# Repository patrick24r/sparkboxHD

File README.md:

# SparkboxHD
Sparkbox, now in 720p!  
The SparkboxHD is a device that will support 2D graphics
                      
### Build and Run
Build using

```
python3 build_sparkbox.py <device>
```

where `<device>` is an existing directory at `device/<device>`.

## MCU
User controller - 2 Analog sticks, 16 Buttons 

### OS
The OS allows the user to choose a level to load

### Levels

#### Loading a level
A level can only be as large as what can fit in memory

Audio data is decompressed and loaded to internal RAM
Video data is loaded to the GPU

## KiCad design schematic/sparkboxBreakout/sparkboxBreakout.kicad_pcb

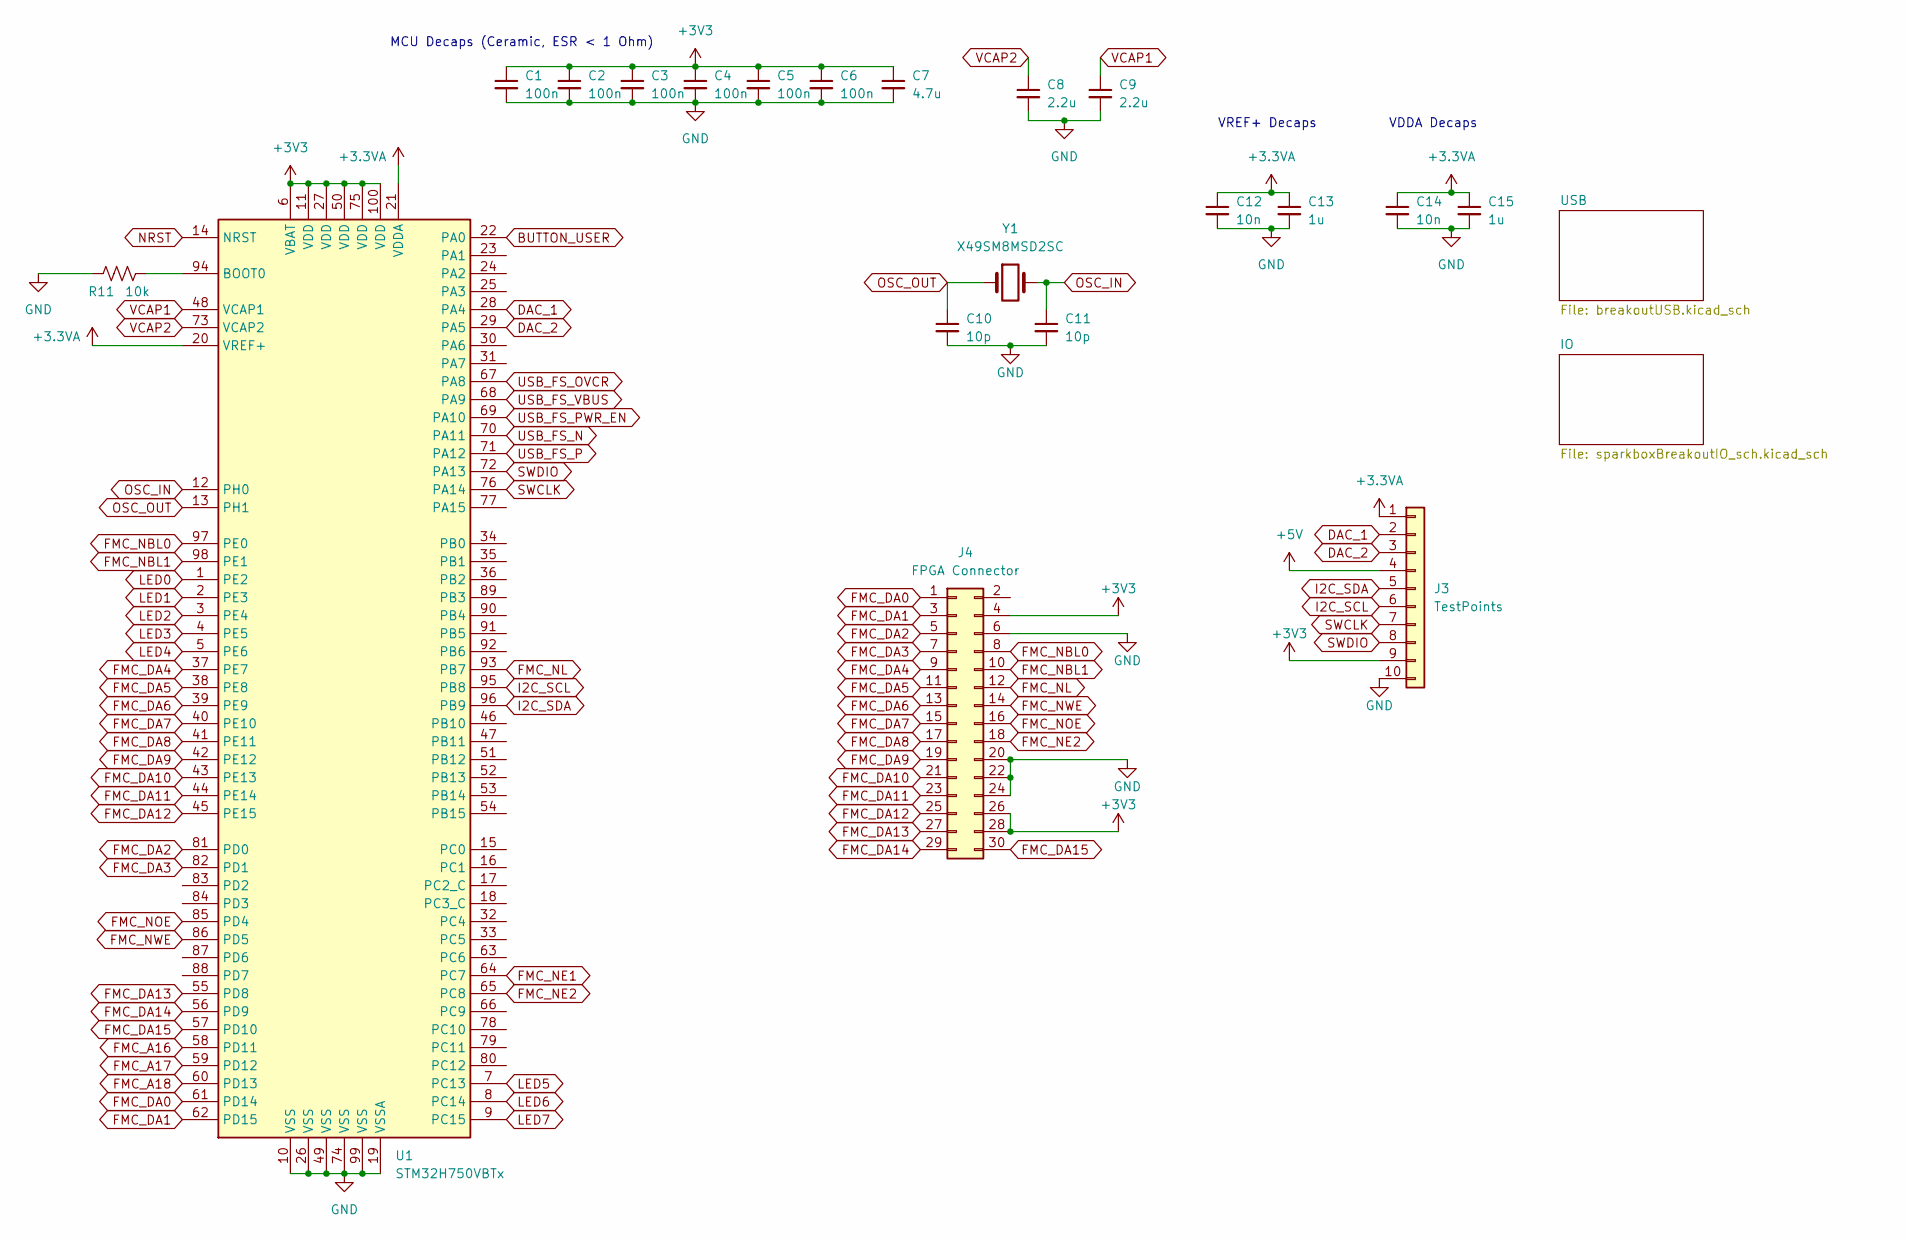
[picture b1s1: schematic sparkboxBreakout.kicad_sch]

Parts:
C1, C2, C3, C4, C5, C6: 100n; C_0402_1005Metric; JLCPCB Part # C1525
C7: 4.7u; C_0402_1005Metric; JLCPCB Part # C23733
C8, C9: 2.2u; C_0402_1005Metric; JLCPCB Part # C12530
C10, C11: 10p; C_0402_1005Metric; JLCPCB Part # C32949
C12, C14: 10n; C_0402_1005Metric; JLCPCB Part # C15195
C13, C15: 1u; C_0402_1005Metric; JLCPCB Part # C52923
J3: TestPoints; PinHeader_1x10_P2.54mm_Vertical; JLCPCB Part # C57369
J4: FPGA Connector; PinHeader_2x15_P2.54mm_Vertical; JLCPCB Part # C56496
R11: 10k; R_0402_1005Metric; JLCPCB Part # C25744
U1: STM32H750VBTx; LQFP-100_14x14mm_P0.5mm; JLCPCB Part # C404010
Y1: X49SM8MSD2SC; Crystal_SMD_HC49-SD; JLCPCB Part # C12674

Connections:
+3.3VA: C12.1, C13.1, C14.1, C15.1, J3.1, U1.20 (VREF+), U1.21 (VDDA); also elsewhere on the board
+3V3: C1.1, C2.1, C3.1, C4.1, C5.1, C6.1, C7.1, J3.9, J4.4, J4.26, J4.28, U1.6 (VBAT), U1.11 (VDD), U1.27 (VDD), U1.50 (VDD), U1.75 (VDD), U1.100 (VDD); also elsewhere on the board
+5V: J3.4; also elsewhere on the board
BUTTON_USER: U1.22 (PA0); also elsewhere on the board
DAC_1: J3.2, U1.28 (PA4)
DAC_2: J3.3, U1.29 (PA5)
FMC_A16: U1.58 (PD11)
FMC_A17: U1.59 (PD12)
FMC_A18: U1.60 (PD13)
FMC_DA0: J4.1, U1.61 (PD14)
FMC_DA1: J4.3, U1.62 (PD15)
FMC_DA2: J4.5, U1.81 (PD0)
FMC_DA3: J4.7, U1.82 (PD1)
FMC_DA4: J4.9, U1.37 (PE7)
FMC_DA5: J4.11, U1.38 (PE8)
FMC_DA6: J4.13, U1.39 (PE9)
FMC_DA7: J4.15, U1.40 (PE10)
FMC_DA8: J4.17, U1.41 (PE11)
FMC_DA9: J4.19, U1.42 (PE12)
FMC_DA10: J4.21, U1.43 (PE13)
FMC_DA11: J4.23, U1.44 (PE14)
FMC_DA12: J4.25, U1.45 (PE15)
FMC_DA13: J4.27, U1.55 (PD8)
FMC_DA14: J4.29, U1.56 (PD9)
FMC_DA15: J4.30, U1.57 (PD10)
FMC_NBL0: J4.8, U1.97 (PE0)
FMC_NBL1: J4.10, U1.98 (PE1)
FMC_NE1: U1.64 (PC7)
FMC_NE2: J4.18, U1.65 (PC8)
FMC_NL: J4.12, U1.93 (PB7)
FMC_NOE: J4.16, U1.85 (PD4)
FMC_NWE: J4.14, U1.86 (PD5)
GND: C1.2, C2.2, C3.2, C4.2, C5.2, C6.2, C7.2, C8.2, C9.2, C10.2, C11.2, C12.2, C13.2, C14.2, C15.2, J3.10, J4.6, J4.20, J4.22, J4.24, R11.2, U1.10 (VSS), U1.19 (VSSA), U1.26 (VSS), U1.49 (VSS), U1.74 (VSS), U1.99 (VSS); also elsewhere on the board
I2C_SCL: J3.6, U1.95 (PB8)
I2C_SDA: J3.5, U1.96 (PB9)
LED0: U1.1 (PE2); also elsewhere on the board
LED1: U1.2 (PE3); also elsewhere on the board
LED2: U1.3 (PE4); also elsewhere on the board
LED3: U1.4 (PE5); also elsewhere on the board
LED4: U1.5 (PE6); also elsewhere on the board
LED5: U1.7 (PC13); also elsewhere on the board
LED6: U1.8 (PC14); also elsewhere on the board
LED7: U1.9 (PC15); also elsewhere on the board
NRST: U1.14 (NRST); also elsewhere on the board
unnamed: R11.1, U1.94 (BOOT0)
OSC_IN: C11.1, U1.12 (PH0), Y1.2
OSC_OUT: C10.1, U1.13 (PH1), Y1.1
SWCLK: J3.7, U1.76 (PA14)
SWDIO: J3.8, U1.72 (PA13)
USB_FS_N: U1.70 (PA11); also elsewhere on the board
USB_FS_OVCR: U1.67 (PA8); also elsewhere on the board
USB_FS_P: U1.71 (PA12); also elsewhere on the board
USB_FS_PWR_EN: U1.69 (PA10); also elsewhere on the board
USB_FS_VBUS: U1.68 (PA9); also elsewhere on the board
VCAP1: C9.1, U1.48 (VCAP1)
VCAP2: C8.1, U1.73 (VCAP2)

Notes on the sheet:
MCU Decaps (Ceramic, ESR < 1 Ohm)
VDDA Decaps
VREF+ Decaps

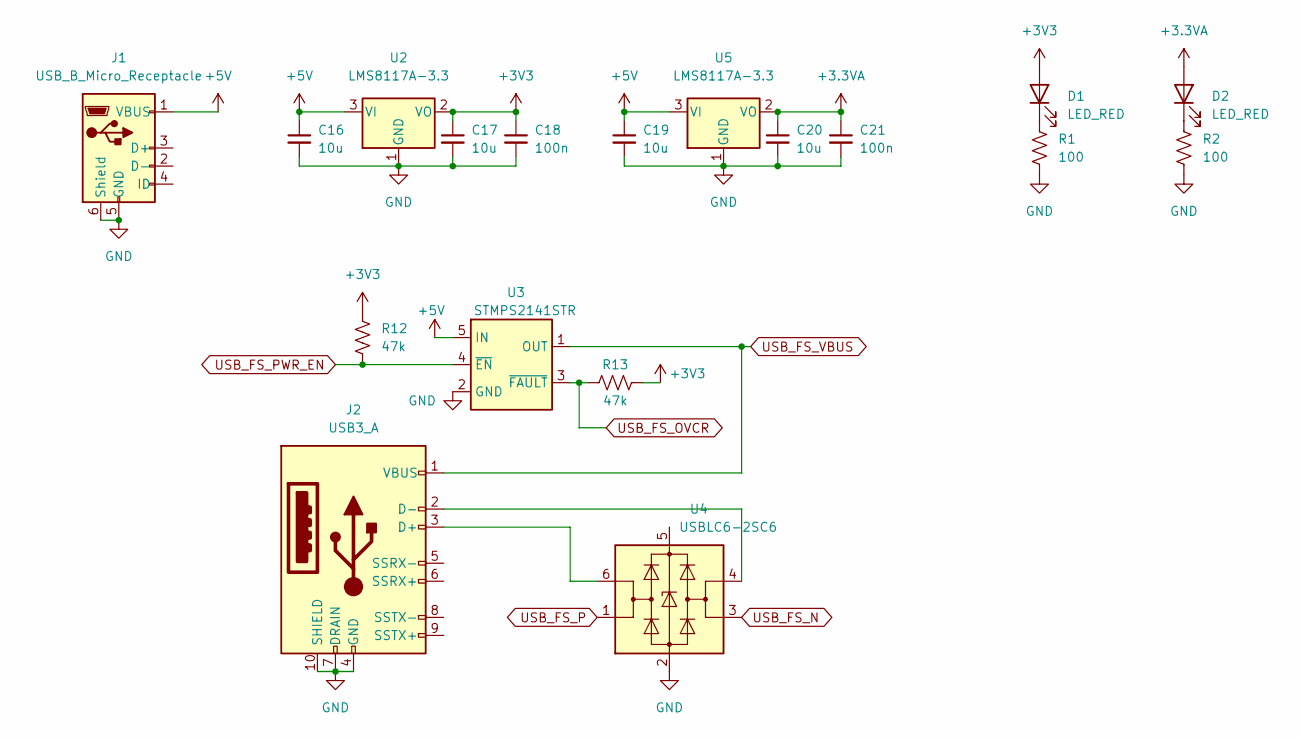
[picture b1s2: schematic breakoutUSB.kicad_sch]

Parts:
C16, C17, C19, C20: 10u; C_0402_1005Metric; JLCPCB Part # C15525
C18, C21: 100n; C_0402_1005Metric; JLCPCB Part # C1525
D1, D2: LED_RED; LED_0603_1608Metric; JLCPCB Part # C2286
J1: USB_B_Micro_Receptacle; USB_Micro_Receptacle_ShouHanMicroQTJ; JLCPCB Part # C404968
J2: USB3_A; USB-A-SMD_U231-091N-4BLRA00-S-1; JLCPCB Part # C381140
R1, R2: 100; R_0402_1005Metric; JLCPCB Part # C25076
R12, R13: 47k; R_0402_1005Metric; JLCPCB Part # C25792
U2, U5: LMS8117A-3.3; SOT-223-3_TabPin2; JLCPCB Part # C201952
U3: STMPS2141STR; SOT-23-5; JLCPCB Part # C54624
U4: USBLC6-2SC6; SOT-23-6; JLCPCB Part # C7519

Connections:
+3.3VA: C20.1, C21.1, D2.2 (A), U5.2 (VO); also elsewhere on the board
+3V3: C17.1, C18.1, D1.2 (A), R12.1, R13.1, U2.2 (VO); also elsewhere on the board
+5V: C16.1, C19.1, J1.1 (VBUS), U2.3 (VI), U3.5 (IN), U5.3 (VI); also elsewhere on the board
GND: C16.2, C17.2, C18.2, C19.2, C20.2, C21.2, J1.5 (GND), J1.6 (Shield), J2.4 (GND), J2.7 (DRAIN), J2.10 (SHIELD), R1.2, R2.2, U2.1 (GND), U3.2 (GND), U4.2 (GND), U5.1 (GND); also elsewhere on the board
unnamed: D1.1 (K), R1.1
unnamed: D2.1 (K), R2.1
unnamed: J2.2 (D-), U4.4 (I/O2)
unnamed: J2.3 (D+), U4.6 (I/O1)
USB_FS_N: U4.3 (I/O2); also elsewhere on the board
USB_FS_OVCR: R13.2, U3.3 (~FAULT); also elsewhere on the board
USB_FS_P: U4.1 (I/O1); also elsewhere on the board
USB_FS_PWR_EN: R12.2, U3.4 (~EN); also elsewhere on the board
USB_FS_VBUS: J2.1 (VBUS), U3.1 (OUT); also elsewhere on the board

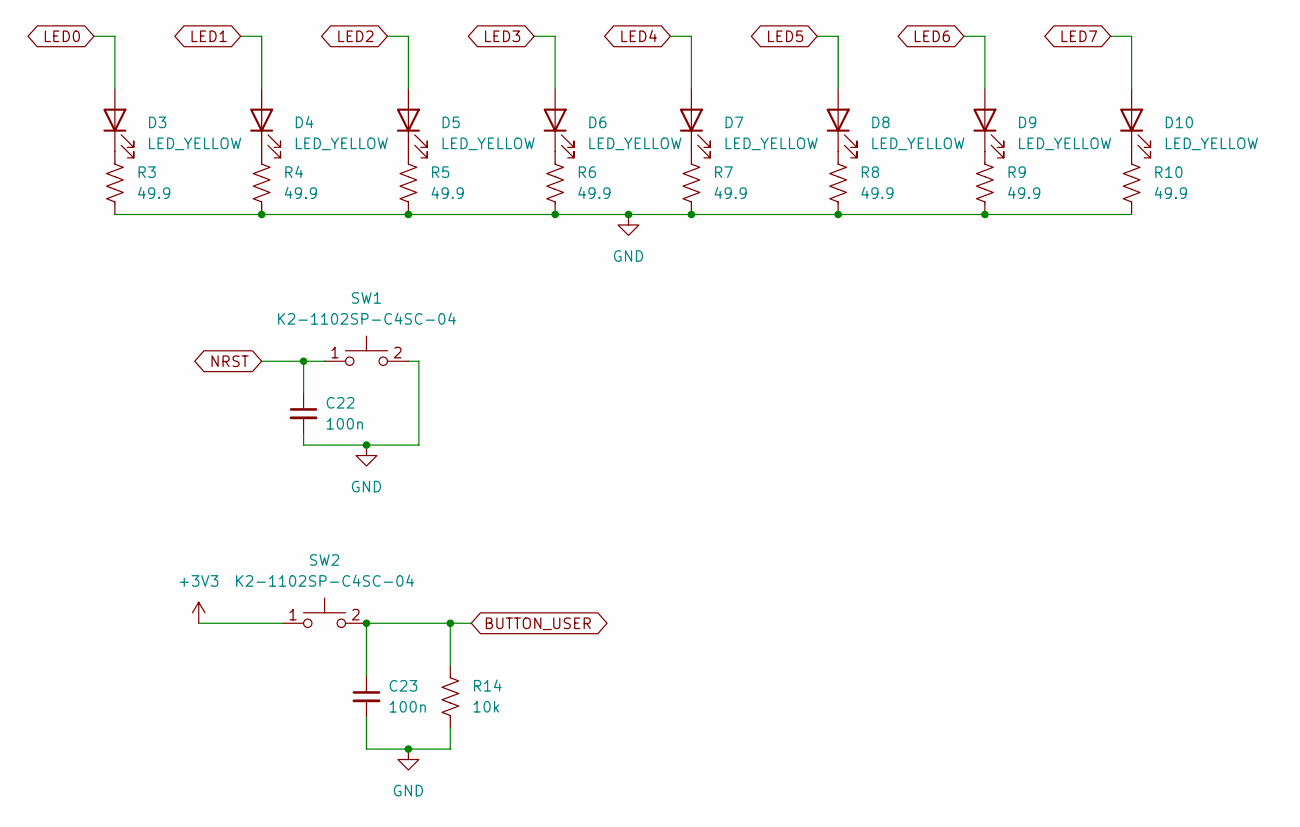
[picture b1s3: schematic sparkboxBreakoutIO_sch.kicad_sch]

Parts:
C22, C23: 100n; C_0402_1005Metric; JLCPCB Part # C1525
D3, D4, D5, D6, D7, D8, D9, D10: LED_YELLOW; LED_0805_2012Metric; JLCPCB Part # C2296
R3, R4, R5, R6, R7, R8, R9, R10: 49.9; R_0402_1005Metric; JLCPCB Part # C25120
R14: 10k; R_0402_1005Metric; JLCPCB Part # C25744
SW1, SW2: K2-1102SP-C4SC-04; KEY-SMD_4P-L6.0-W6.0-P4.50-LS9.5-BL; JLCPCB Part # C127509

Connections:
+3V3: SW2.1; also elsewhere on the board
BUTTON_USER: C23.1, R14.1, SW2.2; also elsewhere on the board
GND: C22.2, C23.2, R3.2, R4.2, R5.2, R6.2, R7.2, R8.2, R9.2, R10.2, R14.2, SW1.2; also elsewhere on the board
LED0: D3.2 (A); also elsewhere on the board
LED1: D4.2 (A); also elsewhere on the board
LED2: D5.2 (A); also elsewhere on the board
LED3: D6.2 (A); also elsewhere on the board
LED4: D7.2 (A); also elsewhere on the board
LED5: D8.2 (A); also elsewhere on the board
LED6: D9.2 (A); also elsewhere on the board
LED7: D10.2 (A); also elsewhere on the board
NRST: C22.1, SW1.1; also elsewhere on the board
unnamed: D3.1 (K), R3.1
unnamed: D4.1 (K), R4.1
unnamed: D5.1 (K), R5.1
unnamed: D6.1 (K), R6.1
unnamed: D7.1 (K), R7.1
unnamed: D8.1 (K), R8.1
unnamed: D9.1 (K), R9.1
unnamed: D10.1 (K), R10.1

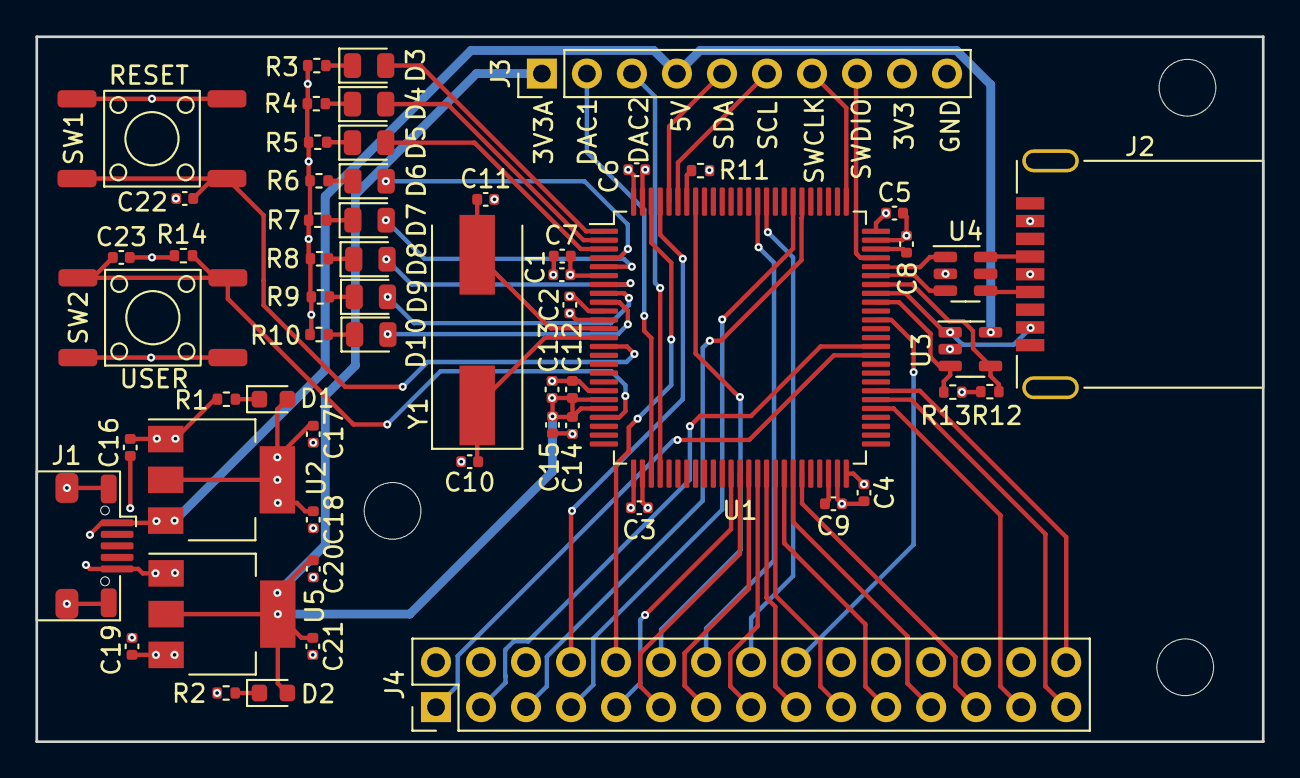
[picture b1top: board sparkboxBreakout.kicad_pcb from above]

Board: 4 copper layers, 69.2 x 39.8 mm, 59 parts (0 on the bottom side), 64 nets.

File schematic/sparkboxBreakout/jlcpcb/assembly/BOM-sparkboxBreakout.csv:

Comment,Designator,Footprint,LCSC
2.2u,"C8,C9",C_0402_1005Metric,C12530
X49SM8MSD2SC,Y1,Crystal_SMD_HC49-SD,C12674
K2-1102SP-C4SC-04,"SW1,SW2",KEY-SMD_4P-L6.0-W6.0-P4.50-LS9.5-BL,C127509
10n,"C12,C14",C_0402_1005Metric,C15195
100n,"C1,C18,C2,C21,C22,C23,C3,C4,C5,C6",C_0402_1005Metric,C1525
10u,"C16,C17,C19,C20",C_0402_1005Metric,C15525
LMS8117A-3.3,"U2,U5",SOT-223-3_TabPin2,C201952
LED_RED,"D1,D2",LED_0603_1608Metric,C2286
LED_YELLOW,"D10,D3,D4,D5,D6,D7,D8,D9",LED_0805_2012Metric,C2296
4.7u,C7,C_0402_1005Metric,C23733
100,"R1,R2",R_0402_1005Metric,C25076
49.9,"R10,R3,R4,R5,R6,R7,R8,R9",R_0402_1005Metric,C25120
10k,"R11,R14",R_0402_1005Metric,C25744
47k,"R12,R13",R_0402_1005Metric,C25792
10p,"C10,C11",C_0402_1005Metric,C32949
USB3_A,J2,USB-A-SMD_U231-091N-4BLRA00-S-1,C381140
STM32H750VBTx,U1,LQFP-100_14x14mm_P0.5mm,C404010
USB_B_Micro_Receptacle,J1,USB_Micro_Receptacle_ShouHanMicroQTJ,C404968
1u,"C13,C15",C_0402_1005Metric,C52923
STMPS2141STR,U3,SOT-23-5,C54624
FPGA Connector,J4,PinHeader_2x15_P2.54mm_Vertical,C56496
TestPoints,J3,PinHeader_1x10_P2.54mm_Vertical,C57369
USBLC6-2SC6,U4,SOT-23-6,C7519

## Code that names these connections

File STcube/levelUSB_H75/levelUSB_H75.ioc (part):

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Mcu.Name=STM32H750VBTx
Mcu.Package=LQFP100
Mcu.UserName=STM32H750VBTx
PA10.GPIOParameters=GPIO_Label
PA10.GPIO_Label=USB_OTG_FS_PWR_EN
PA10.Signal=GPIO_Output
PA11.Mode=Host_Only
PA11.Signal=USB_OTG_FS_DM
PA12.Mode=Host_Only
PA12.Signal=USB_OTG_FS_DP
PA13\ (JTMS/SWDIO).Mode=Serial_Wire
PA13\ (JTMS/SWDIO).Signal=DEBUG_JTMS-SWDIO
PA14\ (JTCK/SWCLK).Mode=Serial_Wire
PA14\ (JTCK/SWCLK).Signal=DEBUG_JTCK-SWCLK
PA4.Signal=COMP_DAC11_group
PA5.Signal=COMP_DAC12_group
PA8.GPIOParameters=GPIO_Label
PA8.GPIO_Label=USB_OTG_FS_OVCR
PA8.Signal=GPXTI8
PA9.Mode=Activate_VBUS
PA9.Signal=USB_OTG_FS_VBUS
PB7.Signal=FMC_NL
PB8.Mode=I2C
PB8.Signal=I2C1_SCL
PB9.Mode=I2C
PB9.Signal=I2C1_SDA
PC13.GPIOParameters=GPIO_Label
PC13.GPIO_Label=LED5
PC13.Signal=GPIO_Output
PC14-OSC32_IN\ (OSC32_IN).GPIOParameters=GPIO_Label
PC14-OSC32_IN\ (OSC32_IN).GPIO_Label=LED6
PC14-OSC32_IN\ (OSC32_IN).Signal=GPIO_Output
PC15-OSC32_OUT\ (OSC32_OUT).GPIOParameters=GPIO_Label
PC15-OSC32_OUT\ (OSC32_OUT).GPIO_Label=LED7
PC15-OSC32_OUT\ (OSC32_OUT).Signal=GPIO_Output
PC8.Mode=NorPsramChipSelect2_1
PC8.Signal=FMC_NE2
PD0.Signal=FMC_D2_DA2
PD1.Signal=FMC_D3_DA3
PD10.Signal=FMC_D15_DA15
PD14.Signal=FMC_D0_DA0
PD15.Signal=FMC_D1_DA1
PD4.Signal=FMC_NOE
PD5.Signal=FMC_NWE
PD8.Signal=FMC_D13_DA13
PD9.Signal=FMC_D14_DA14
PE0.Signal=FMC_NBL0
PE1.Signal=FMC_NBL1
PE10.Signal=FMC_D7_DA7
PE11.Signal=FMC_D8_DA8
PE12.Signal=FMC_D9_DA9
PE13.Signal=FMC_D10_DA10
PE14.Signal=FMC_D11_DA11
PE15.Signal=FMC_D12_DA12
PE2.GPIOParameters=GPIO_Label
PE2.GPIO_Label=LED0
PE2.Signal=GPIO_Output
PE3.GPIOParameters=GPIO_Label
PE3.GPIO_Label=LED1
PE3.Signal=GPIO_Output
PE4.GPIOParameters=GPIO_Label
PE4.GPIO_Label=LED2
PE4.Signal=GPIO_Output
PE5.GPIOParameters=GPIO_Label
PE5.GPIO_Label=LED3
PE5.Signal=GPIO_Output
PE6.GPIOParameters=GPIO_Label
PE6.GPIO_Label=LED4
PE6.Signal=GPIO_Output
PE7.Signal=FMC_D4_DA4
PE8.Signal=FMC_D5_DA5
PE9.Signal=FMC_D6_DA6
PH0-OSC_IN\ (PH0).Mode=HSE-External-Oscillator
PH0-OSC_IN\ (PH0).Signal=RCC_OSC_IN
PH1-OSC_OUT\ (PH1).Mode=HSE-External-Oscillator
PH1-OSC_OUT\ (PH1).Signal=RCC_OSC_OUT
RCC.HSE_VALUE=8000000
RCC.SYSCLKFreq_VALUE=240000000
RCC.SYSCLKSource=RCC_SYSCLKSOURCE_PLLCLK
board=custom

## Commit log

2019-09-15 Initial files for gpu and cpu
2019-09-15 Started quartus project for GPU
2019-09-28 Rebased code, updated STCube project, converting to SystemVerilog
2019-09-28 Added stcube gnerated code
2019-09-29 Major organizational updates, folder restructuring
2019-10-04 Updated gpu verilog files to add command buffer
2019-10-04 Added RAM layer initial files
2019-10-05 Added sdram controller using intel IP
2019-10-07 GPU verilog synthesizes now
2019-10-10 Pixel counter pipe simulated and working
2019-10-11 Pipes 0 and 2 simulated and working?
2019-10-11 Pipes 0-2 simulated and working. Pipe 2 (Address calculation) is suspect
2019-11-13 Major updates to gpu cpu
2019-11-13 Updated gitignore to ignore verilog simulation results
2019-11-13 Unfortunately looks like 1080p isn't feasible for an FPGA at 400 MHz :(
2019-11-18 Added Sparkbox class to initialize all sparkbox peripherals
2019-11-24 Layer and psparkbox class updates
2019-12-10 Added preliminary controller code for f0, updated command interface
2019-12-16 added LCD interface to GPU
2019-12-17 lcd timing simmed and works (probably)
2019-12-19 added lcd controller with simulation
2020-01-01 Updated pin assignments for fpga board
2020-01-01 Used for testing pin assignments, works for LEDs
2020-01-13 Code works on FPGA, cpu class structure updated
2020-02-03 Updated Audio and Video cpu class files
2020-02-04 Updated code generation
2020-02-15 Updated game code
2020-02-28 lcd tester works! We have color!
2020-03-08 Updated gpu, cpu files, fpga teal code included
2020-03-10 Working on de0nano sdram
2020-03-16 Updated audio files, lcd tester
2020-07-01 Started transition to system verilog
2020-07-03 SDRAM WORKS FINALLY
2020-07-12 ram and flash address calculations work :P
2020-07-13 Added RAM block
2020-07-18 added untested palette memory
2020-07-22 Cache will not work, moving away from it for now
2020-07-31 ram block appears to simulate correctly for controller reads/writes
2020-08-01 gpu ram pipeline consecutive reads needs work
2020-08-07 Removed gpu, it is in a separate repo now
2020-08-22 already have blinking lights on the disco board, stcube is so helpful
2020-09-01 Trying to get SD card to work, narrowed the problem down to HAL_SD_ConfigWideBusOperation
2020-11-17 SD card works, refactoring audio control class
2021-08-02 stcube rebuild for new stm32h7 device
2021-08-04 Hey, it builds so it's gotta work
2021-08-06 Transitioned sparkbox classes to use global variables
2021-08-17 USB reads/writes are finally working! Onto sdram and audio file playing
2021-08-18 Audio timer callback works to toggle an LED, hopefully thebugs are minimal
2021-12-08 Start of structure refactor
2021-12-08 Removed old folder, added nem common folder
2021-12-08 Folder name change
2021-12-09 Got one makefile sorted
2021-12-11 It compiles :O
2021-12-11 It compiles and there is LED blinking. MAJOR success
2021-12-12 Debugging works, trying to figure out USB again
2022-01-11 One day later, suddenly it all works again
2022-01-11 Importing audio files hard faults when writing to an external memory that isn't connected. Who would have thunk
2022-04-03 Added custom PCB schematic, converted project to stm32h750
2023-04-10 cmake restructure
2023-04-13 Basic sparkbox compiles on host with cmake
2023-04-15 posix filesystem driver works
2023-04-15 Added support for windows filesystems
2023-04-16 Logging works, added windows device
2023-04-16 Controller driver compiles
2023-04-16 Migrated to managers over controllers for less confusion
2023-04-17 Updated file driver
2023-04-22 Updated filesystem driver to handle directory searching
2023-08-30 Added functions to create and remove directories
2023-08-30 Added FreeRTOS submodule
2023-08-30 Reconfigured to use freertos in project
2023-09-06 Update controller driver interface, added asserts, updated filesystem calls
2023-09-09 Controller task gets successfully created. Now to see if it runs...
2023-10-08 Added build script and stm nucleo_h743zi2 device
2023-10-08 Build script works to build posix
2023-10-12 Compiles for nucleo board
2023-10-12 Added board initialization
2023-10-15 compiles but doesn't run on device
2023-10-28 First step toward proper linking
2024-05-02 Fixed file name in logging macro
2024-05-02 Updated build path, audio driver
2024-05-03 Added (not completely functional) support for importing wav files
2024-05-06 audio imports files, posix scheduler runs
2024-05-08 Moved queue and task managenment to shared code
2024-05-18 Partial updates to resampler
2024-05-25 Host audio driver changes, nearly functional
2024-05-25 Use forked FreeRTOS repo for header include collision prevention
2024-05-26 Host audio driver outputs wav file, but all samples are 0...
2024-05-27 Audio outputs a (kind of) valid file on posix. Audio at half speed
2024-05-27 Updated file stream calls and restore original file write position
2025-01-17 Migrate to new host system
2025-01-17 Cmake refactor
2025-01-18 sparkbox is now loaded at runtime. New interfaces for managers expose usage
2025-01-19 Moved sparkbox files to align with namespaces, support any number of audio files being loaded
2025-01-19 Messages are now dynamically allocated so senders and receivers do not need to manage it
2025-01-19 Move library loading to core app driver
2025-01-20 Now works to dynamically load levels
2025-01-20 Modified structure related to library loading, windows almost compiles again
2025-01-20 Sounds now import, next need to get playback working
2025-03-11 Updated build script, dynamic libs now link properly
2025-03-13 Fixed compile errors for native ubuntu
